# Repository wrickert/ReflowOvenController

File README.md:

# ReflowOvenController
Reflow oven controller using the 2019 BSidesIowa badge. Runs on micropython. <br>

***USE AT YOUR OWN RISK*** I have used this code but there are still potentially bugs that if left unmonitored could cause a fire.

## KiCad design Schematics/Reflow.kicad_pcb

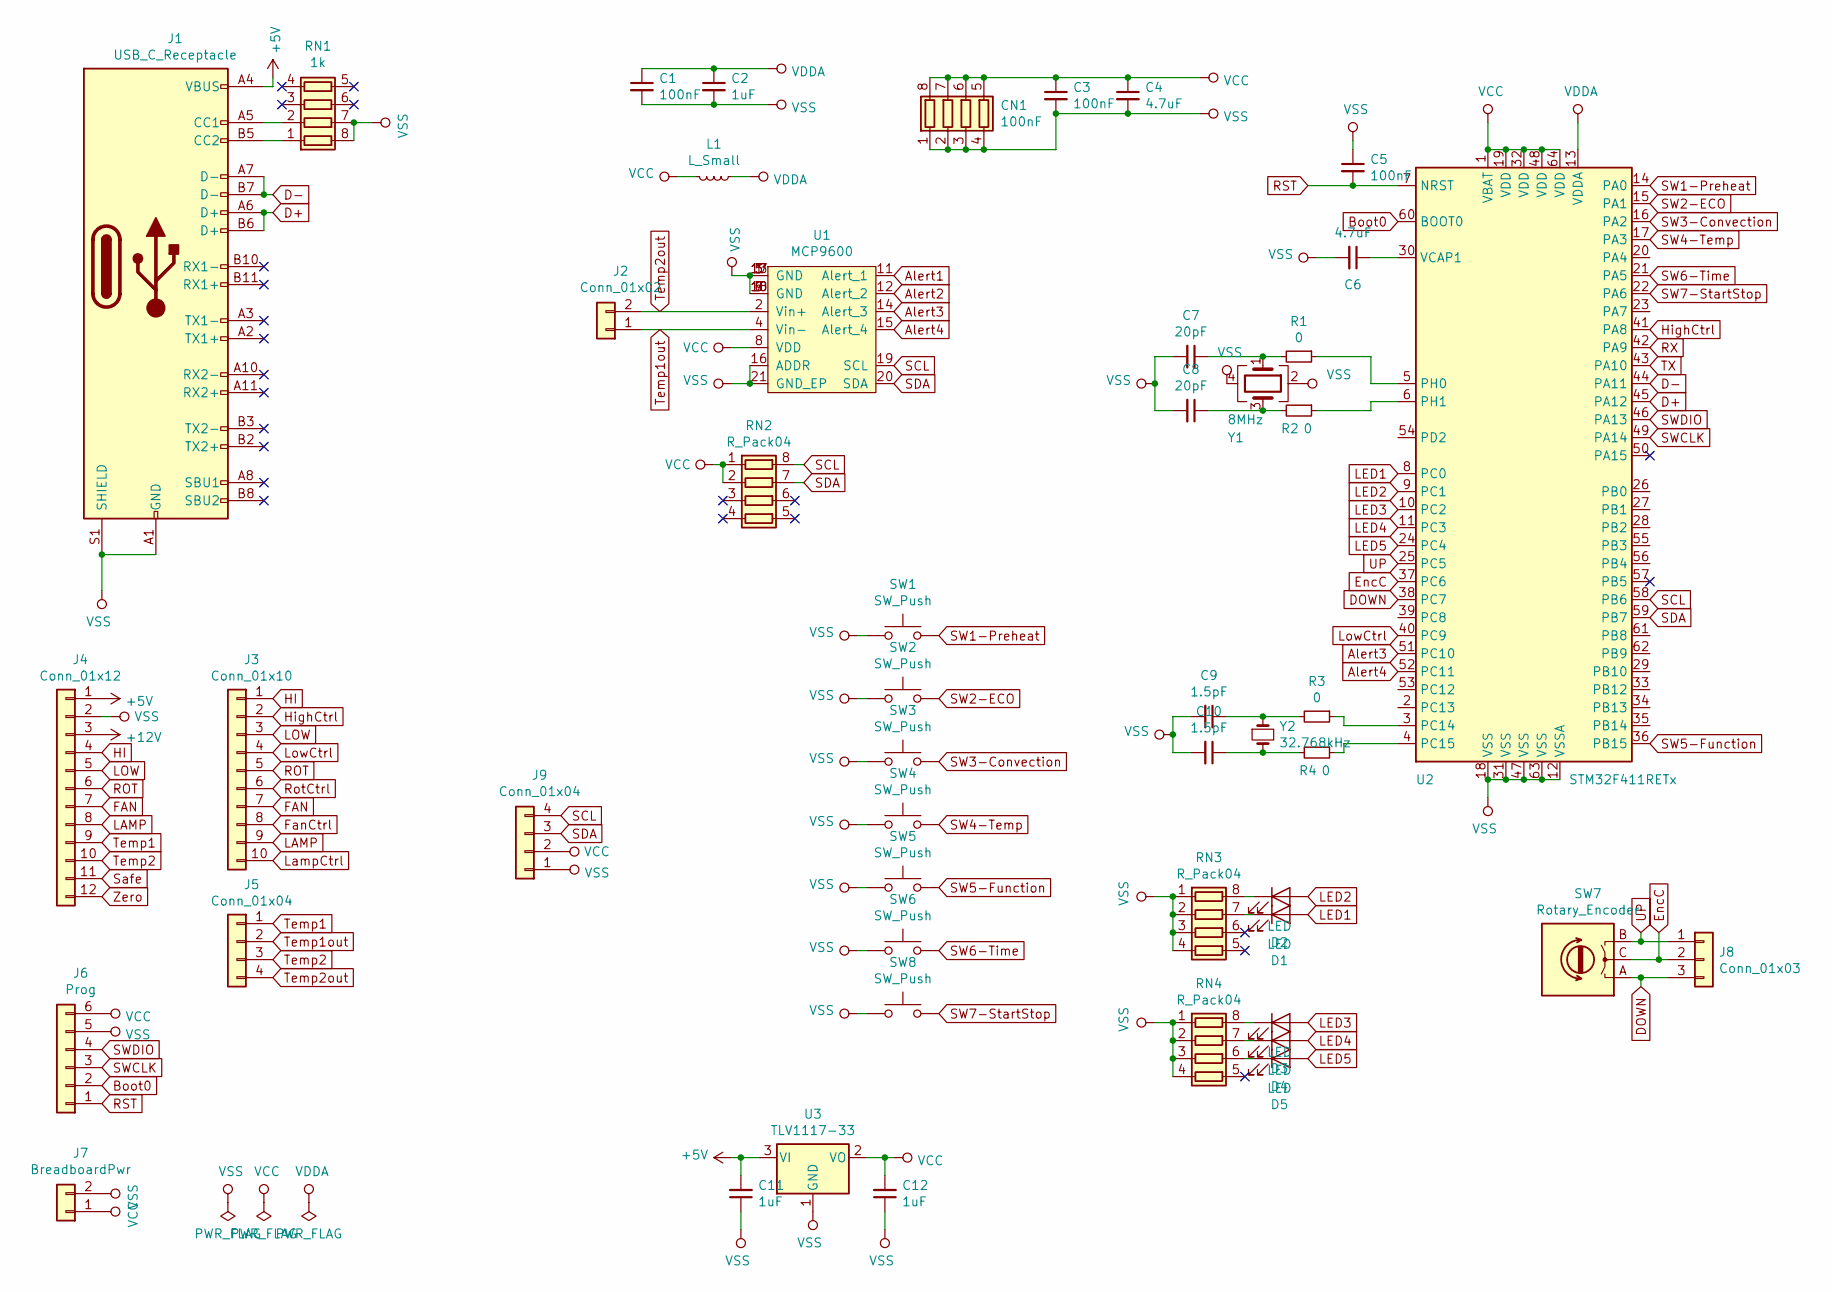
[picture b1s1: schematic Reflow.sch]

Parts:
C1, C3, C5: 100nF; C_0805_2012Metric
C2, C11, C12: 1uF; C_0805_2012Metric
C4, C6: 4.7uF; C_0805_2012Metric
C7, C8: 20pF; C_0805_2012Metric
C9, C10: 1.5pF; C_0805_2012Metric
CN1: 100nF; R_Array_Convex_4x0603
D1, D2, D3, D4, D5: LED; LED_0805_2012Metric
J1: USB_C_Receptacle; Jing_USB-C_Vert_C168703
J2: Conn_01x02; Connector_1x02_5mm
J3: Conn_01x10; PinHeader_1x10_P2.54mm_Vertical
J4: Conn_01x12; A2501WR-12P1-Conn
J5, J9: Conn_01x04; PinHeader_1x04_P2.54mm_Vertical
J6: Prog; PinHeader_1x06_P2.54mm_Vertical
J7: BreadboardPwr; PinHeader_1x02_P2.54mm_Vertical
J8: Conn_01x03; PinHeader_1x03_P2.54mm_Vertical
L1: L_Small; L_0603_1608Metric
R1, R2, R3, R4: 0; R_0805_2012Metric
RN1: 1k; R_Array_Convex_4x0603
RN2, RN3, RN4: R_Pack04; R_Array_Convex_4x0603
SW1, SW2, SW3, SW4, SW5, SW6, SW8: SW_Push; SW_Push_1P1T_NO_6x6mm_H9.5mm
SW7: Rotary_Encoder; Circular_Rotary_Enc
U1: MCP9600; QFN-20-1EP_5x5mm_P0.65mm_EP3.35x3.35mm
U2: STM32F411RETx; LQFP-64_10x10mm_P0.5mm
U3: TLV1117-33; SOT-223-3_TabPin2
Y1: 8MHz; Crystal_SMD_SeikoEpson_TSX3225-4Pin_3.2x2.5mm
Y2: 32.768kHz; Crystal_SMD_3215-2Pin_3.2x1.5mm

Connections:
+5V: C11.2, J1.A4 (VBUS), J1.A9 (VBUS), J1.B4 (VBUS), J1.B9 (VBUS), J4.1, U3.3 (VI)
+12V: J4.3
Alert1: U1.11 (Alert_1)
Alert2: U1.12 (Alert_2)
Alert3: U1.14 (Alert_3), U2.51 (PC10)
Alert4: U1.15 (Alert_4), U2.52 (PC11)
Boot0: J6.2, U2.60 (BOOT0)
D+: J1.A6 (D+), J1.B6 (D+), U2.45 (PA12)
D-: J1.A7 (D-), J1.B7 (D-), U2.44 (PA11)
DOWN: J8.3, SW7.A, U2.38 (PC7)
EncC: J8.2, SW7.C, U2.37 (PC6)
FAN: J3.7, J4.7
FanCtrl: J3.8
HI: J3.1, J4.4
HighCtrl: J3.2, U2.41 (PA8)
LAMP: J3.9, J4.8
LED1: D1.2 (A), U2.8 (PC0)
LED2: D2.2 (A), U2.9 (PC1)
LED3: D3.2 (A), U2.10 (PC2)
LED4: D4.2 (A), U2.11 (PC3)
LED5: D5.2 (A), U2.24 (PC4)
LOW: J3.3, J4.5
LampCtrl: J3.10
LowCtrl: J3.4, U2.40 (PC9)
unnamed: C6.1, U2.30 (VCAP1)
unnamed: C7.1, R1.2, Y1.1
unnamed: C8.1, R2.2, Y1.3
unnamed: C9.1, R3.2, Y2.1
unnamed: C10.1, R4.2, Y2.2
unnamed: D1.1 (K), RN3.7 (R2.2)
unnamed: D2.1 (K), RN3.8 (R1.2)
unnamed: D3.1 (K), RN4.8 (R1.2)
unnamed: D4.1 (K), RN4.7 (R2.2)
unnamed: D5.1 (K), RN4.6 (R3.2)
unnamed: J1.A5 (CC1), RN1.2 (R2.1)
unnamed: J1.B5 (CC2), RN1.1 (R1.1)
unnamed: R1.1, U2.5 (PH0)
unnamed: R2.1, U2.6 (PH1)
unnamed: R3.1, U2.3 (PC14)
unnamed: R4.1, U2.4 (PC15)
ROT: J3.5, J4.6
RST: C5.2, J6.1, U2.7 (NRST)
RX: U2.42 (PA9)
RotCtrl: J3.6
SCL: J9.4, RN2.8 (R1.2), U1.19 (SCL), U2.58 (PB6)
SDA: J9.3, RN2.7 (R2.2), U1.20 (SDA), U2.59 (PB7)
SW1-Preheat: SW1.2, U2.14 (PA0)
SW2-ECO: SW2.2, U2.15 (PA1)
SW3-Convection: SW3.2, U2.16 (PA2)
SW4-Temp: SW4.2, U2.17 (PA3)
SW5-Function: SW5.2, U2.36 (PB15)
SW6-Time: SW6.2, U2.21 (PA5)
SW7-StartStop: SW8.2, U2.22 (PA6)
SWCLK: J6.3, U2.49 (PA14)
SWDIO: J6.4, U2.46 (PA13)
Safe: J4.11
TX: U2.43 (PA10)
Temp1: J4.9, J5.1
Temp1out: J2.1, J5.2, U1.4 (Vin-)
Temp2: J4.10, J5.3
Temp2out: J2.2, J5.4, U1.2 (Vin+)
UP: J8.1, SW7.B, U2.25 (PC5)
VCC: C3.1, C4.1, C12.2, CN1.5 (R4.2), CN1.6 (R3.2), CN1.7 (R2.2), CN1.8 (R1.2), J6.6, J7.1, J9.2, L1.2, RN2.1 (R1.1), RN2.2 (R2.1), U1.8 (VDD), U2.1 (VBAT), U2.19 (VDD), U2.32 (VDD), U2.48 (VDD), U2.64 (VDD), U3.2 (VO)
VDDA: C1.1, C2.1, L1.1, U2.13 (VDDA)
VSS: C1.2, C2.2, C3.2, C4.2, C5.1, C6.2, C7.2, C8.2, C9.2, C10.2, C11.1, C12.1, CN1.1 (R1.1), CN1.2 (R2.1), CN1.3 (R3.1), CN1.4 (R4.1), J1.A1 (GND), J1.A12 (GND), J1.B1 (GND), J1.B12 (GND), J1.S1 (SHIELD), J4.2, J6.5, J7.2, J9.1, RN1.7 (R2.2), RN1.8 (R1.2), RN3.1 (R1.1), RN3.2 (R2.1), RN3.3 (R3.1), RN3.4 (R4.1), RN4.1 (R1.1), RN4.2 (R2.1), RN4.3 (R3.1), RN4.4 (R4.1), SW1.1, SW2.1, SW3.1, SW4.1, SW5.1, SW6.1, SW8.1, U1.1 (GND), U1.3 (GND), U1.5 (GND), U1.6 (GND), U1.7 (GND), U1.9 (GND), U1.10 (GND), U1.13 (GND), U1.16 (ADDR), U1.17 (GND), U1.18 (GND), U1.21 (GND_EP), U2.12 (VSSA), U2.18 (VSS), U2.31 (VSS), U2.47 (VSS), U2.63 (VSS), U3.1 (GND), Y1.2, Y1.4
Zero: J4.12

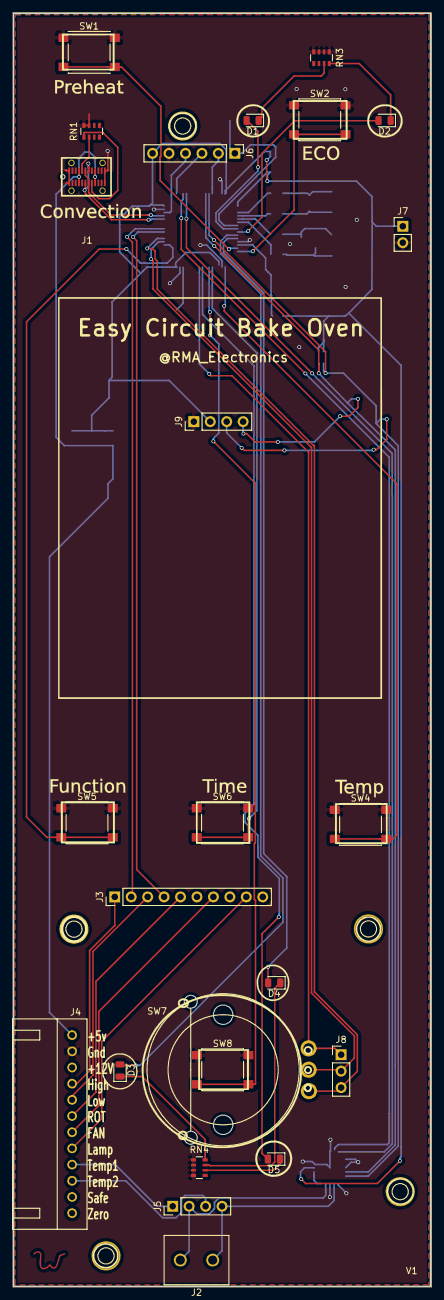
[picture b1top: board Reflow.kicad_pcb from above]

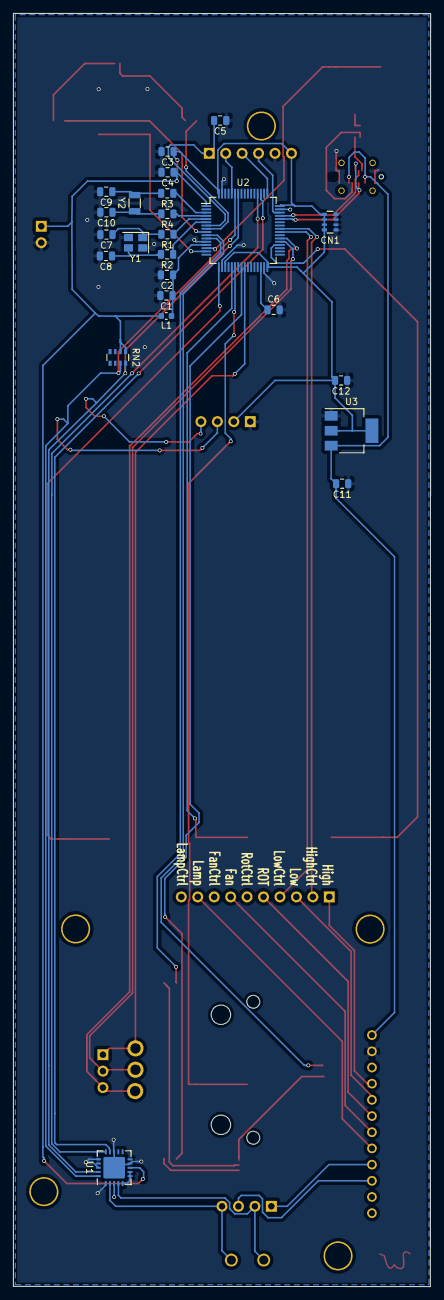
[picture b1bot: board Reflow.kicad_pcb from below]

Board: 2 copper layers, 64.4 x 196.6 mm, 49 parts (24 on the bottom side), 55 nets.

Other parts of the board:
Ref**: Val**; W

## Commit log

2019-04-11 Pid control done, next to add a reflow profile
2019-04-11 I think v1 is done, lets see if I burn the house down
2019-04-13 Hey, it actually turns off when it should now
2019-04-21 Added to readme
2019-04-22 Changed code to get rid of unintended recursion
2019-04-23 Added penny control
2020-03-21 Finally completed V1 control board
